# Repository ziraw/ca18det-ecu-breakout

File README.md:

# CA18DET ECU Breakout PCB
for prototyping eg. Speeduino and such.

UNTESTED!!! This has not yet been built or tested, pinout from https://support.haltech.com/portal/en/kb/articles/ca18-engine

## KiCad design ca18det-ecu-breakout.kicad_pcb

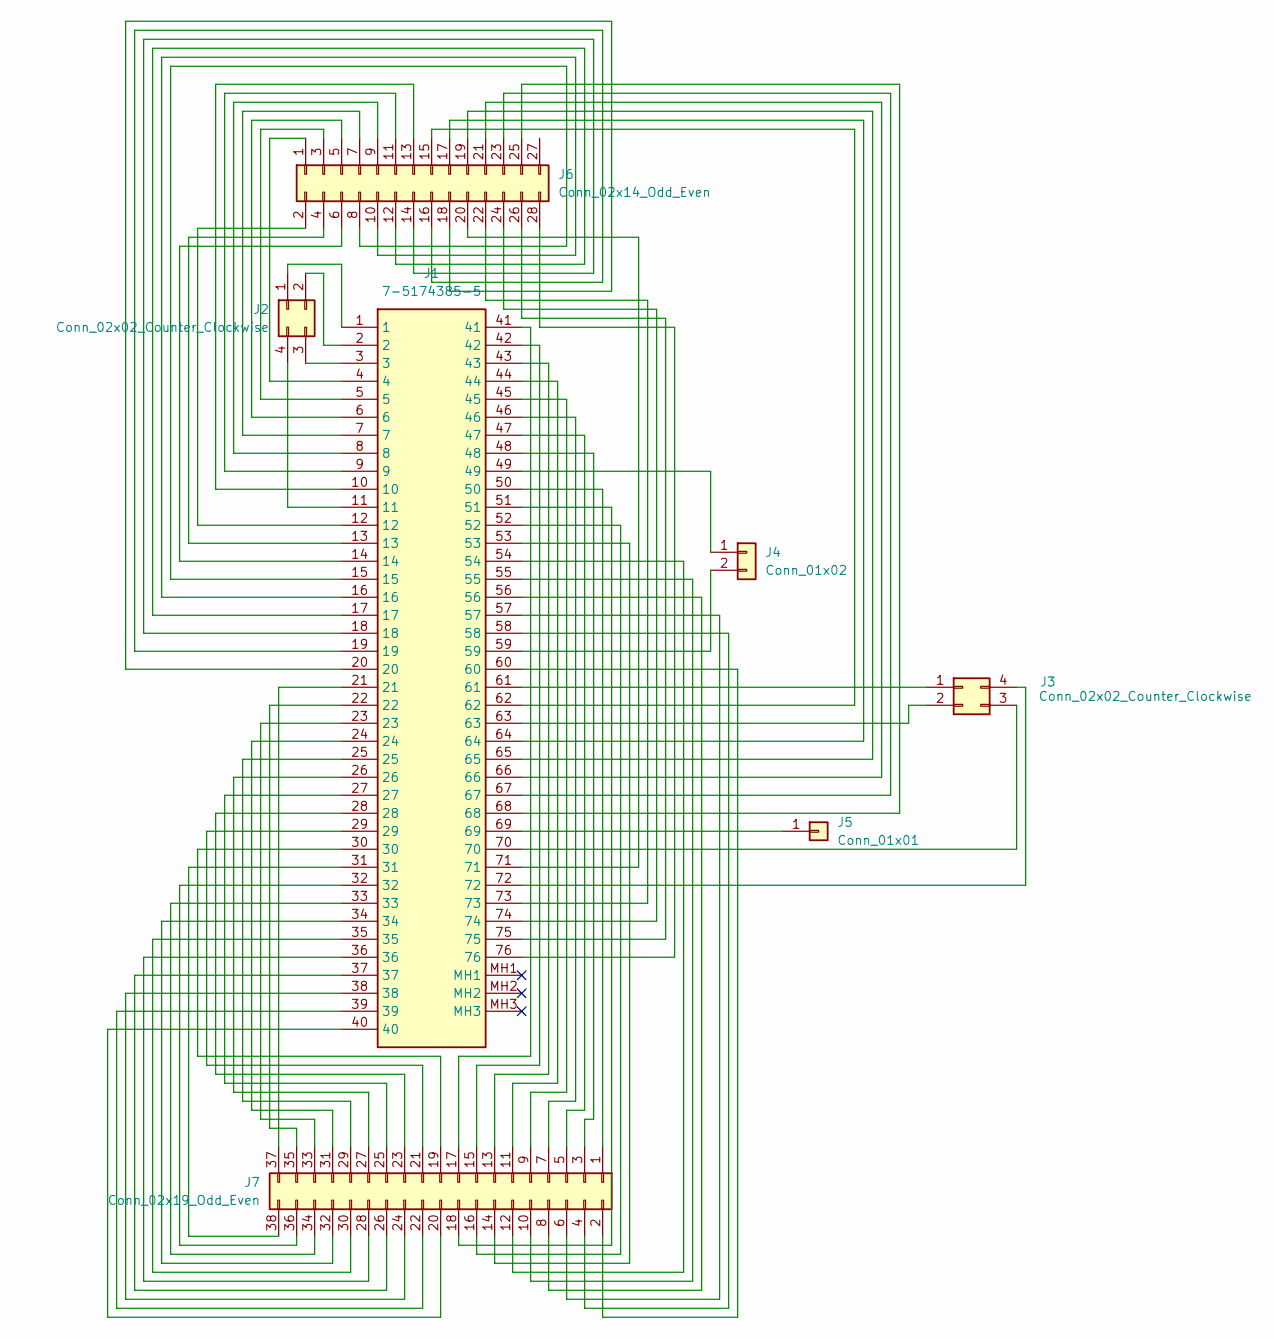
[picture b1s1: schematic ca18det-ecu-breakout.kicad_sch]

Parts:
J1: 7-5174385-5; 751743855; Manufacturer_Part_Number 7-5174385-5; Mouser Part Number 571-7-5174385-5
J2, J3: Conn_02x02_Counter_Clockwise; PinHeader_2x02_P2.54mm_Vertical
J4: Conn_01x02; PinHeader_1x02_P2.54mm_Vertical
J5: Conn_01x01; PinHeader_1x01_P2.54mm_Vertical
J6: Conn_02x14_Odd_Even; PinHeader_2x14_P2.54mm_Vertical
J7: Conn_02x19_Odd_Even; PinHeader_2x19_P2.54mm_Vertical

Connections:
GND: J1.MH1, J1.MH2, J1.MH3
unnamed: J1.1, J2.1
unnamed: J1.2, J2.2
unnamed: J1.3, J2.3
unnamed: J1.11, J2.4
unnamed: J1.61, J3.1
unnamed: J1.63, J3.2
unnamed: J1.70, J3.3
unnamed: J1.72, J3.4
unnamed: J1.49, J4.1
unnamed: J1.59, J4.2
unnamed: J1.69, J5.1
unnamed: J1.4, J6.1
unnamed: J1.12, J6.2
unnamed: J1.5, J6.3
unnamed: J1.13, J6.4
unnamed: J1.6, J6.5
unnamed: J1.14, J6.6
unnamed: J1.7, J6.7
unnamed: J1.15, J6.8
unnamed: J1.8, J6.9
unnamed: J1.16, J6.10
unnamed: J1.9, J6.11
unnamed: J1.17, J6.12
unnamed: J1.10, J6.13
unnamed: J1.18, J6.14
unnamed: J1.62, J6.15
unnamed: J1.19, J6.16
unnamed: J1.64, J6.17
unnamed: J1.20, J6.18
unnamed: J1.65, J6.19
unnamed: J1.71, J6.20
unnamed: J1.66, J6.21
unnamed: J1.73, J6.22
unnamed: J1.67, J6.23
unnamed: J1.74, J6.24
unnamed: J1.68, J6.25
unnamed: J1.75, J6.26
unnamed: J1.76, J6.28
unnamed: J1.50, J7.1
unnamed: J1.60, J7.2
unnamed: J1.48, J7.3
unnamed: J1.58, J7.4
unnamed: J1.47, J7.5
unnamed: J1.57, J7.6
unnamed: J1.46, J7.7
unnamed: J1.56, J7.8
unnamed: J1.45, J7.9
unnamed: J1.55, J7.10
unnamed: J1.44, J7.11
unnamed: J1.54, J7.12
unnamed: J1.43, J7.13
unnamed: J1.53, J7.14
unnamed: J1.42, J7.15
unnamed: J1.52, J7.16
unnamed: J1.41, J7.17
unnamed: J1.51, J7.18
unnamed: J1.30, J7.19
unnamed: J1.40, J7.20
unnamed: J1.29, J7.21
unnamed: J1.39, J7.22
unnamed: J1.28, J7.23
unnamed: J1.38, J7.24
unnamed: J1.27, J7.25
unnamed: J1.37, J7.26
unnamed: J1.26, J7.27
unnamed: J1.36, J7.28
unnamed: J1.25, J7.29
unnamed: J1.35, J7.30
unnamed: J1.24, J7.31
unnamed: J1.34, J7.32
unnamed: J1.23, J7.33
unnamed: J1.33, J7.34
unnamed: J1.22, J7.35
unnamed: J1.32, J7.36
unnamed: J1.21, J7.37
unnamed: J1.31, J7.38

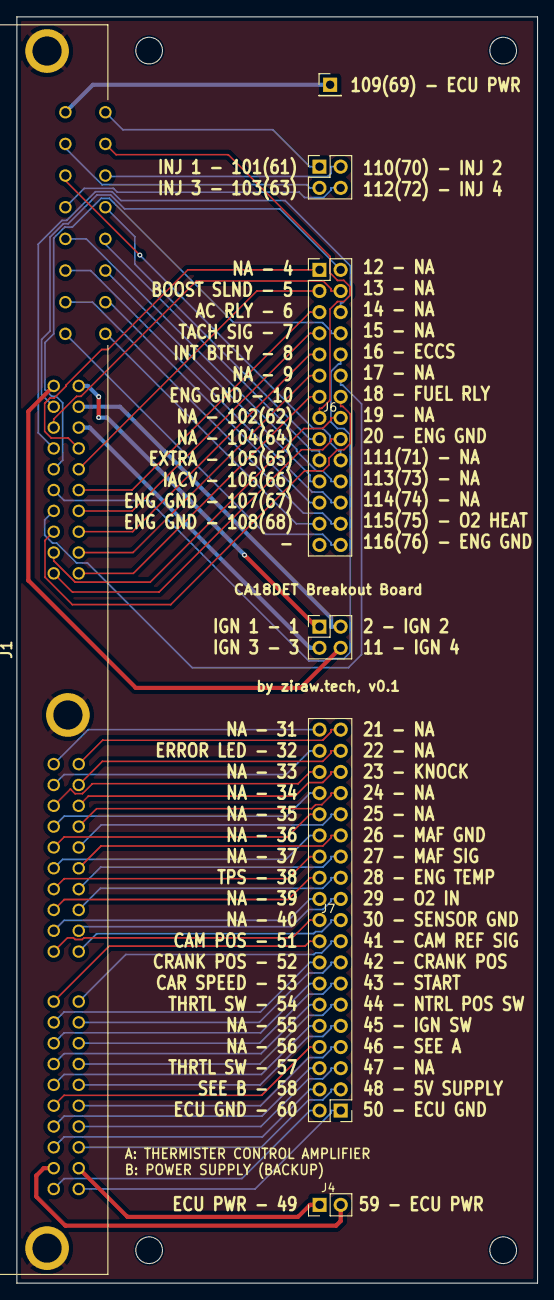
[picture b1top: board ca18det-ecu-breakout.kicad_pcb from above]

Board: 2 copper layers, 62.5 x 152.0 mm, 11 parts (0 on the bottom side), 77 nets.

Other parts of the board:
H1, H2, H3, H4: MountingHole; MountingHole_3.2mm_M3

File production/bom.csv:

Designator,Footprint,Quantity,Value,LCSC Part #
J1,751743855,1,7-5174385-5,
"J2, J3",PinHeader_2x02_P2.54mm_Vertical,2,Conn_02x02_Counter_Clockwise,
J4,PinHeader_1x02_P2.54mm_Vertical,1,Conn_01x02,
J5,PinHeader_1x01_P2.54mm_Vertical,1,Conn_01x01,
J6,PinHeader_2x14_P2.54mm_Vertical,1,Conn_02x14_Odd_Even,
J7,PinHeader_2x19_P2.54mm_Vertical,1,Conn_02x19_Odd_Even,
